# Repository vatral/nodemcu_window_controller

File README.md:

# nodemcu_window_controller
Window open/close controller

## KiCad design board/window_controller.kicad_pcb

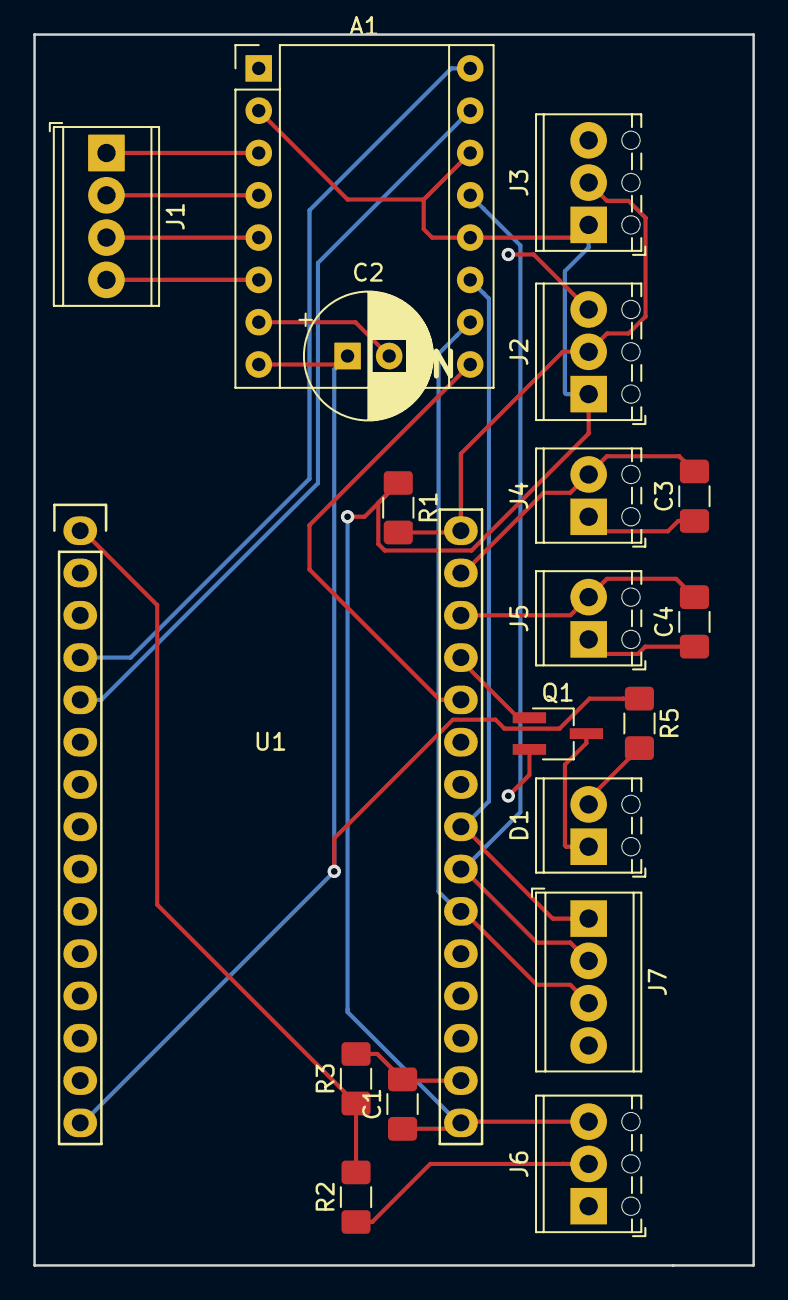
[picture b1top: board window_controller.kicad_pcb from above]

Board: 2 copper layers, 43.2 x 73.9 mm, 19 parts (0 on the bottom side), 21 nets.

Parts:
A1: Pololu_Breakout_A4988; Pololu_Breakout-16_15.2x20.3mm
C1, C3, C4: 100 nF; C_1206_3216Metric_Pad1.42x1.75mm_HandSolder
C2: 100 uF; CP_Radial_D7.5mm_P2.50mm
D1: LED; TerminalBlock_Phoenix_MPT-0,5-2-2.54_1x02_P2.54mm_Horizontal
J1: Motor; TerminalBlock_Phoenix_MPT-0,5-4-2.54_1x04_P2.54mm_Horizontal
J2: Temp 1; TerminalBlock_Phoenix_MPT-0,5-3-2.54_1x03_P2.54mm_Horizontal
J3: Temp 2; TerminalBlock_Phoenix_MPT-0,5-3-2.54_1x03_P2.54mm_Horizontal
J4: Limit: Open; TerminalBlock_Phoenix_MPT-0,5-2-2.54_1x02_P2.54mm_Horizontal
J5: Limit: Close; TerminalBlock_Phoenix_MPT-0,5-2-2.54_1x02_P2.54mm_Horizontal
J6: Rain; TerminalBlock_Phoenix_MPT-0,5-3-2.54_1x03_P2.54mm_Horizontal
J7: SPI; TerminalBlock_Phoenix_MPT-0,5-4-2.54_1x04_P2.54mm_Horizontal
Q1: Q_NPN_BEC; TSOT-23_HandSoldering
R1: 4.7k; R_1206_3216Metric_Pad1.42x1.75mm_HandSolder
R2: 10k; R_1206_3216Metric_Pad1.42x1.75mm_HandSolder
R3: 4.3k; R_1206_3216Metric_Pad1.42x1.75mm_HandSolder
R5: 100; R_1206_3216Metric_Pad1.42x1.75mm_HandSolder
U1: NodeMCU_Amica_R2

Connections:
+3V3: A1.2, A1.12, A1.14, C1.1, J2.1, J3.1, J6.3, R1.1, U1.16
/1WIRE: J2.2, J3.2, R1.2, U1.30
/CLK: A1.11, J7.1, U1.23
/DIR: A1.16, U1.4
/ENABLE: A1.9, U1.26
/LIMIT_CLOSED: C4.2, J5.2, U1.28
/LIMIT_OPEN: C3.2, J4.2, U1.29
/MISO: A1.13, J7.2, U1.22
/MOSI: A1.10, J7.3, U1.21
/RAIN: R2.2, R3.1, U1.1
/REMOTE_LED: Q1.1, U1.27
/STEP: A1.15, U1.5
GND: A1.1, A1.7, C1.2, C2.2, C3.1, C4.1, J2.3, J3.3, J4.1, J5.1, J6.1, J7.4, Q1.2, R3.2, U1.14, U1.17
unnamed: A1.3, J1.1
unnamed: A1.4, J1.2
unnamed: A1.5, J1.3
unnamed: A1.6, J1.4
unnamed: D1.1, Q1.3
unnamed: D1.2, R5.2
unnamed: J6.2, R2.1
VCC: A1.8, C2.1, R5.1, U1.15

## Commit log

2018-09-21 Initial version
